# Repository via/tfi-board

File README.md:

# Testing hardware for TFI-computer

## Analog
Schematic and PCB for external TLC2543-based ADC board

 - Separate 5V supply to ADC and external sensors
 - Dedicated protected inputs for:
     * Battery Reference Voltage
     * Intake Temperature
     * Coolant Temperature
     * Throttle Position
     * Exhaust Gas Oxygen
     * Spare Thermistor
 - Addititional 5 unprotected inputs
 - SPI interface, and end-of-conversion output

## IO
Schematic and PCB for various digital IO and drivers

- 4x 0.5 Amp, 12 Volt ignition outputs
- 2x 2 Amp, 12 Volt high-side driver outputs
- 4x 2 Amp injector drivers
- 2x 2 amp low-side drivers
- CAN driver (Remove 3.3 V Zener to use 5V logic lines)
- 2 protected digital inputs

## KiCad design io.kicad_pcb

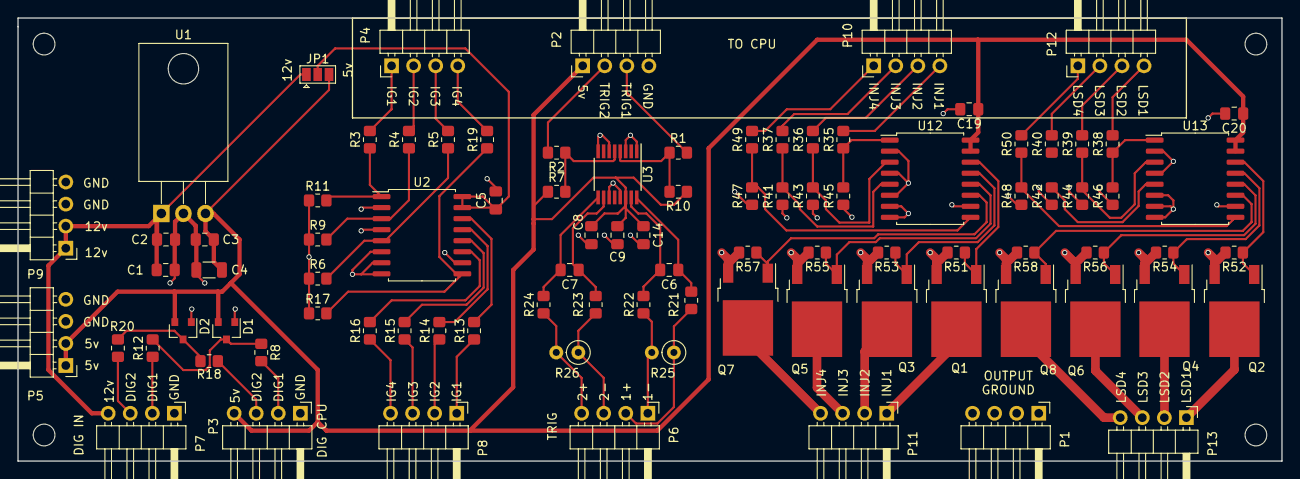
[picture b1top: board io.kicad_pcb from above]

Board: 2 copper layers, 145.5 x 51.0 mm, 91 parts (0 on the bottom side), 71 nets.

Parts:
C1: 10 uF; C_0805_2012Metric_Pad1.18x1.45mm_HandSolder
C2, C3: 0.1 uF; C_0805_2012Metric_Pad1.18x1.45mm_HandSolder
C4: 47 uF; C_1206_3216Metric
C5, C19, C20: 1 uF; C_0805_2012Metric_Pad1.18x1.45mm_HandSolder
C6, C7: 1n; C_0805_2012Metric_Pad1.18x1.45mm_HandSolder
C8: 10n; C_0805_2012Metric_Pad1.18x1.45mm_HandSolder
C9: 0.1u; C_0805_2012Metric_Pad1.18x1.45mm_HandSolder
C14: 1u; C_0805_2012Metric_Pad1.18x1.45mm_HandSolder
D1, D2: BAT54S; SOT-23
JP1: IG_PWR; SolderJumper-3_P1.3mm_Open_Pad1.0x1.5mm
P1: OUT_GND; PinHeader_1x04_P2.54mm_Horizontal
P2: TRIG-cpu; PinHeader_1x04_P2.54mm_Horizontal
P3: DIG-CPU; PinHeader_1x04_P2.54mm_Horizontal
P4: IN-CPU; PinHeader_1x04_P2.54mm_Horizontal
P5: CPU_PWR; PinHeader_1x04_P2.54mm_Horizontal
P6: TRIG-IN; PinHeader_1x04_P2.54mm_Horizontal
P7: DIG-IN; PinHeader_1x04_P2.54mm_Horizontal
P8: IGNITION; PinHeader_1x04_P2.54mm_Horizontal
P9: PWR_IN; PinHeader_1x04_P2.54mm_Horizontal
P10: INJ-CPU; PinHeader_1x04_P2.54mm_Horizontal
P11: INJECTORS; PinHeader_1x04_P2.54mm_Horizontal
P12: LSD-CPU; PinHeader_1x04_P2.54mm_Horizontal
P13: LSDS; PinHeader_1x04_P2.54mm_Horizontal
Q1, Q2, Q3, Q4, Q5, Q6, Q7, Q8: MOSFET; TO-252-2
R1, R2, R3, R4, R5, R8, R12, R18, R19, R20, R21, R22, R23, R24, R35, R36, R37, R38, R39, R40, R49, R50: 1k; R_0805_2012Metric_Pad1.20x1.40mm_HandSolder
R6, R9, R11, R17, R41, R42, R43, R44, R45, R46, R47, R48, R51, R52, R53, R54, R55, R56, R57, R58: 100k; R_0805_2012Metric_Pad1.20x1.40mm_HandSolder
R7, R10: 10k; R_0805_2012Metric_Pad1.20x1.40mm_HandSolder
R13, R14, R15, R16: 150; R_0805_2012Metric_Pad1.20x1.40mm_HandSolder
R25, R26: 330; R_Axial_DIN0207_L6.3mm_D2.5mm_P2.54mm_Vertical
U1: LM2940; TO-220-3_Horizontal_TabDown
U2, U12, U13: MIC4469; SOIC-16W_7.5x10.3mm_P1.27mm
U3: MAX9926UAEE+; QSOP-16_3.9x4.9mm_P0.635mm

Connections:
5v: C3.1, C4.1, C8.1, C9.1, C14.1, C19.1, C20.1, D1.2, D2.2, JP1.3, P2.1, P3.4, P5.1, P5.2, R7.1, R10.1, U1.3, U3.14, U12.15, U12.16, U13.15, U13.16
12v_power: C1.1, C2.1, JP1.1, P7.4, P9.1, P9.2, U1.1
DIG1-cpu: P3.2, R8.2
DIG1-in: P7.2, R12.1
DIG2-cpu: P3.3, R18.2
DIG2-in: P7.3, R20.1
GND: C1.2, C2.2, C3.2, C4.2, C5.2, C8.2, C9.2, C14.2, C19.2, C20.2, D1.1, D2.1, P2.4, P3.1, P5.3, P5.4, P7.1, P9.3, P9.4, R6.1, R9.1, R11.1, R17.1, R41.1, R42.1, R43.1, R44.1, R45.1, R46.1, R47.1, R48.1, U1.2, U2.2, U2.4, U2.6, U2.7, U2.8, U2.10, U3.1, U3.3, U3.6, U3.8, U3.11, U3.13, U12.2, U12.4, U12.6, U12.7, U12.8, U12.10, U13.2, U13.4, U13.6, U13.7, U13.8, U13.10
IG1-cpu: P4.1, R3.2
IG1-out: P8.1, R13.1
IG2-cpu: P4.2, R4.2
IG2-out: P8.2, R14.1
IG3-cpu: P4.3, R5.2
IG3-out: P8.3, R15.1
IG4-cpu: P4.4, R19.2
IG4-out: P8.4, R16.1
INJ1-cpu: P10.4, R35.2
INJ1-out: P11.1, Q1.2
INJ2-cpu: P10.3, R36.2
INJ2-out: P11.2, Q3.2
INJ3-cpu: P10.2, R37.2
INJ3-out: P11.3, Q5.2
INJ4-cpu: P10.1, R49.2
INJ4-out: P11.4, Q7.2
LSD1-cpu: P12.4, R38.2
LSD1-out: P13.1, Q2.2
LSD2-cpu: P12.3, R39.2
LSD2-out: P13.2, Q4.2
LSD3-cpu: P12.2, R40.2
LSD3-out: P13.3, Q6.2
LSD4-cpu: P12.1, R50.2
LSD4-out: P13.4, Q8.2
unnamed: C5.1, JP1.2, U2.15, U2.16
unnamed: C6.1, R21.2, U3.16
unnamed: C6.2, R22.2, U3.15
unnamed: C7.1, R23.2, U3.10
unnamed: C7.2, R24.2, U3.9
unnamed: D1.3, R8.1, R12.2
unnamed: D2.3, R18.1, R20.2
unnamed: Q1.1, R51.1, U12.14
unnamed: Q2.1, R52.1, U13.14
unnamed: Q3.1, R53.1, U12.13
unnamed: Q4.1, R54.1, U13.13
unnamed: Q5.1, R55.1, U12.12
unnamed: Q6.1, R56.1, U13.12
unnamed: Q7.1, R57.1, U12.11
unnamed: Q8.1, R58.1, U13.11
unnamed: R1.1, R10.2, U3.4
unnamed: R2.1, R7.2, U3.5
unnamed: R4.1, R9.2, U2.3
unnamed: R5.1, R6.2, U2.5
unnamed: R3.1, R11.2, U2.1
unnamed: R13.2, U2.14
unnamed: R14.2, U2.13
unnamed: R15.2, U2.12
unnamed: R16.2, U2.11
unnamed: R17.2, R19.1, U2.9
unnamed: R35.1, R45.2, U12.1
unnamed: R36.1, R43.2, U12.3
unnamed: R37.1, R41.2, U12.5
unnamed: R38.1, R46.2, U13.1
unnamed: R39.1, R44.2, U13.3
unnamed: R40.1, R42.2, U13.5
unnamed: R47.2, R49.1, U12.9
unnamed: R48.2, R50.1, U13.9
OUT_GND: P1.1, P1.2, P1.3, P1.4, Q1.3, Q2.3, Q3.3, Q4.3, Q5.3, Q6.3, Q7.3, Q8.3, R51.2, R52.2, R53.2, R54.2, R55.2, R56.2, R57.2, R58.2
TRIG1: P2.3, R1.2
TRIG1IN+: P6.2, R21.1, R25.1
TRIG1IN-: P6.1, R22.1, R25.2
TRIG2: P2.2, R2.2
TRIG2IN+: P6.4, R24.1, R26.2
TRIG2IN-: P6.3, R23.1, R26.1

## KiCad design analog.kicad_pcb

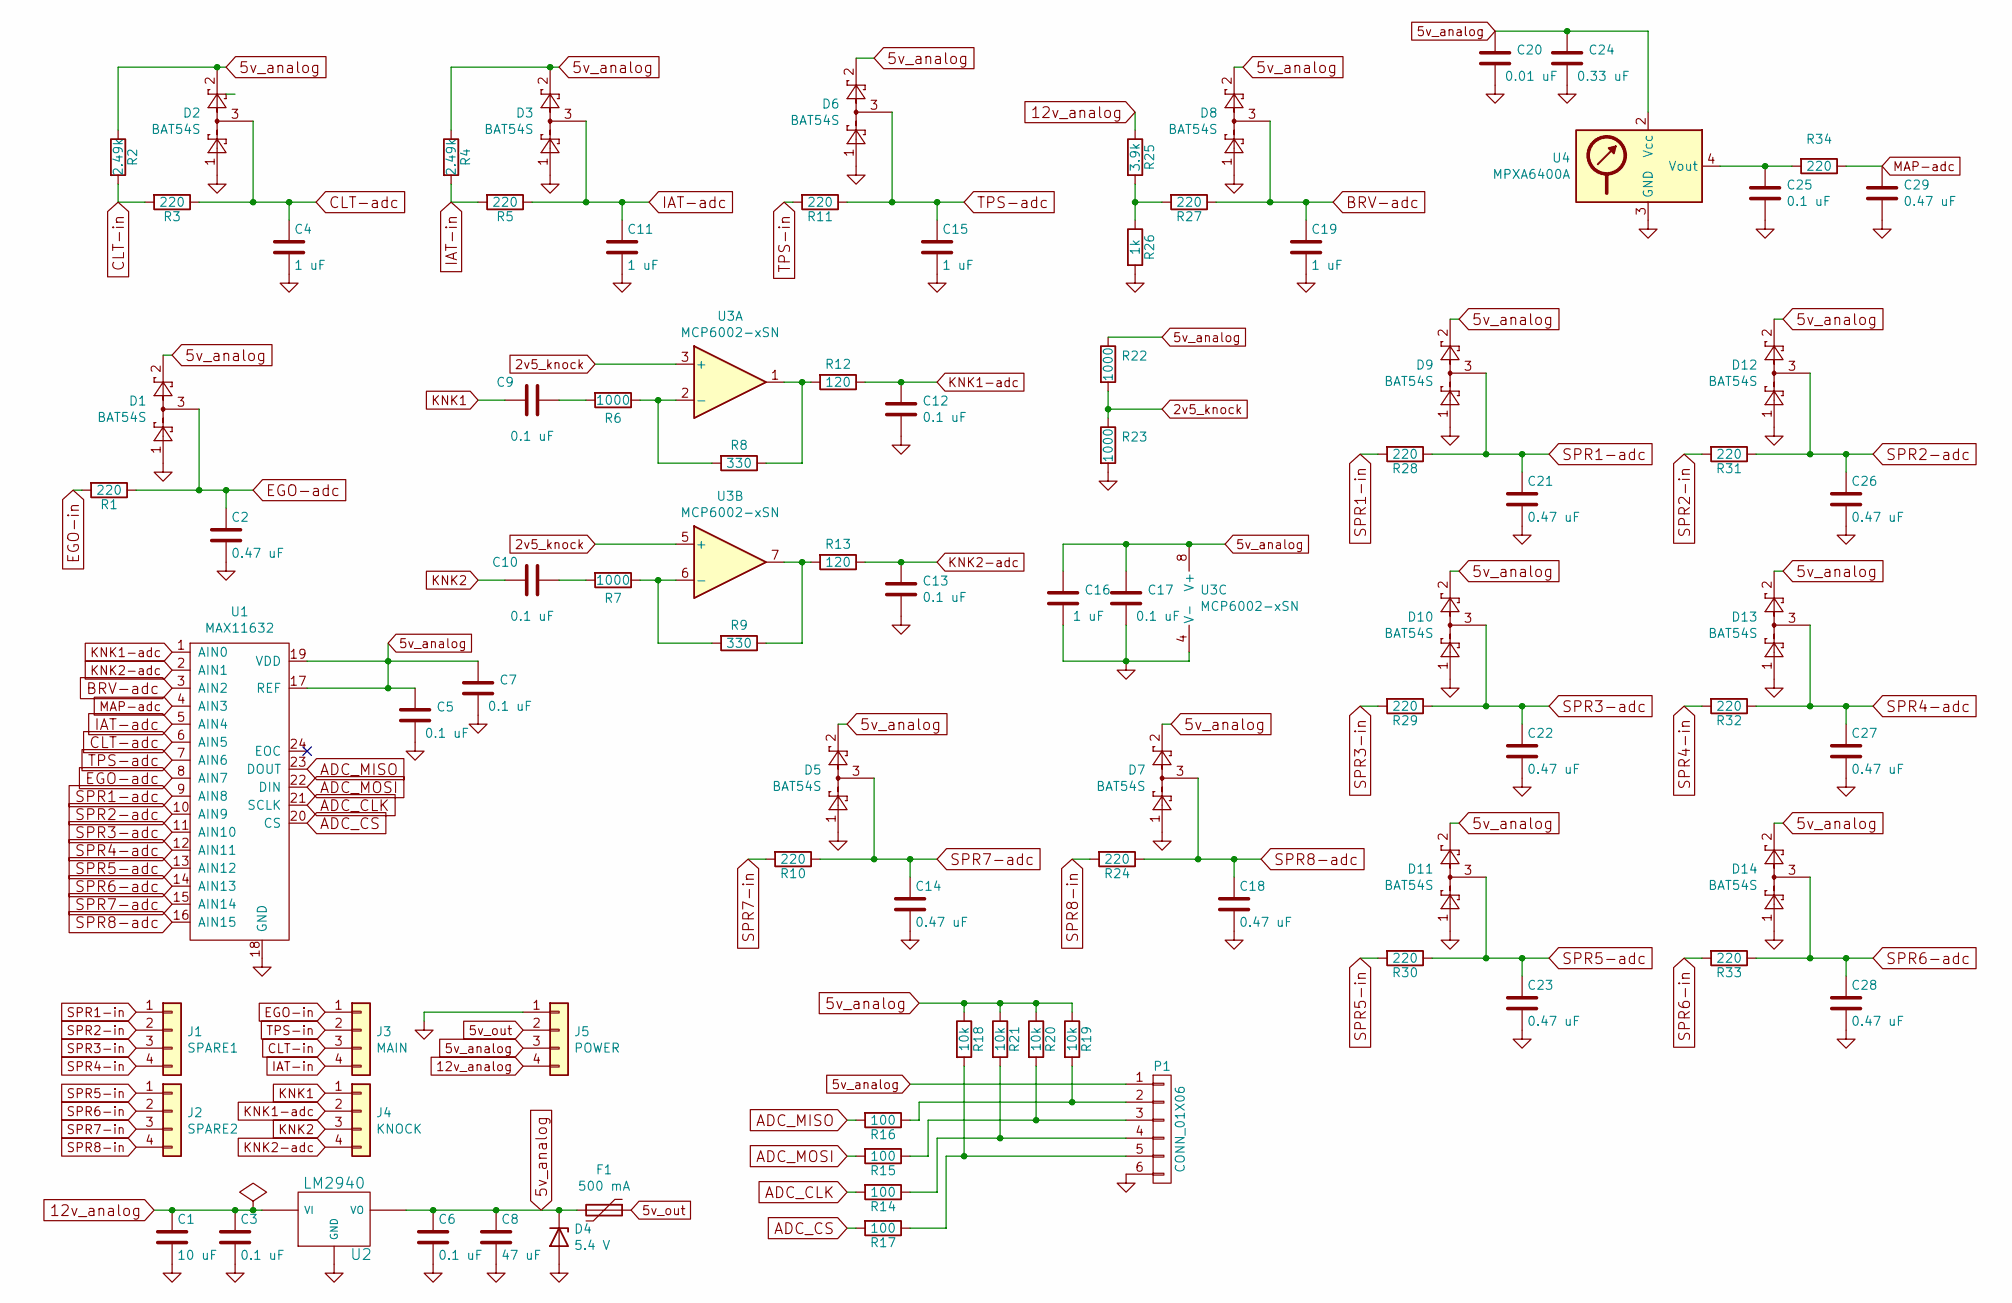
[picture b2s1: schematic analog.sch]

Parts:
C1: 10 uF; C_0805_2012Metric_Pad1.18x1.45mm_HandSolder; Rating 35V Tantalum
C2, C14, C18, C21, C22, C23, C26, C27, C28, C29: 0.47 uF; C_0805_2012Metric_Pad1.18x1.45mm_HandSolder
C3, C5, C6, C7, C9, C10, C12, C13, C17, C25: 0.1 uF; C_0805_2012Metric_Pad1.18x1.45mm_HandSolder
C4, C11, C15, C16, C19: 1 uF; C_0805_2012Metric_Pad1.18x1.45mm_HandSolder
C8: 47 uF; C_1206_3216Metric_Pad1.33x1.80mm_HandSolder; Rating 10 V Tantalum
C20: 0.01 uF; C_0805_2012Metric_Pad1.18x1.45mm_HandSolder
C24: 0.33 uF; C_0805_2012Metric_Pad1.18x1.45mm_HandSolder
D1, D2, D3, D5, D6, D7, D8, D9, D10, D11, D12, D13, D14: BAT54S; SOT-23
D4: 5.4 V; D_A-405_P2.54mm_Vertical_AnodeUp
F1: 500 mA; Fuse_1206_3216Metric_Pad1.42x1.75mm_HandSolder
J1: SPARE1; PinHeader_1x04_P2.54mm_Horizontal
J2: SPARE2; PinHeader_1x04_P2.54mm_Horizontal
J3: MAIN; PinHeader_1x04_P2.54mm_Horizontal
J4: KNOCK; PinHeader_1x04_P2.54mm_Horizontal
J5: POWER; PinHeader_1x04_P2.54mm_Horizontal
P1: CONN_01X06; PinHeader_1x06_P2.54mm_Horizontal
R1, R3, R5, R10, R11, R24, R27, R28, R29, R30, R31, R32, R33, R34: 220; R_0805_2012Metric_Pad1.20x1.40mm_HandSolder
R2, R4: 2.49k; R_0805_2012Metric_Pad1.20x1.40mm_HandSolder; Rating 0.1%
R6, R7, R22, R23: 1000; R_0805_2012Metric_Pad1.20x1.40mm_HandSolder
R8, R9: 330; R_0805_2012Metric_Pad1.20x1.40mm_HandSolder
R12, R13: 120; R_0805_2012Metric_Pad1.20x1.40mm_HandSolder
R14, R15, R16, R17: 100; R_0805_2012Metric_Pad1.20x1.40mm_HandSolder
R18, R19, R20, R21: 10k; R_0805_2012Metric_Pad1.20x1.40mm_HandSolder
R25: 3.9k; R_0805_2012Metric_Pad1.20x1.40mm_HandSolder; Rating 0.1%
R26: 1k; R_0805_2012Metric_Pad1.20x1.40mm_HandSolder; Rating 0.1%
U1: MAX11632; QSOP-24_3.9x8.7mm_P0.635mm
U2: LM2940; TO-220-3_Horizontal_TabDown
U3: MCP6002-xSN; MSOP-8_3x3mm_P0.65mm
U4: MPXA6400A; Freescale_98ARH99089A

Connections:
2v5_knock: R22.2, R23.1, U3.3 (+), U3.5 (+)
5v_analog: C5.1, C6.1, C7.1, C8.1, C16.1, C17.1, C20.1, C24.1, D1.2, D2.2, D3.2, D4.1 (K), D5.2, D6.2, D7.2, D8.2, D9.2, D10.2, D11.2, D12.2, D13.2, D14.2, F1.2, J5.3, P1.1, R2.1, R4.1, R18.1, R19.1, R20.1, R21.1, R22.1, U1.17 (REF), U1.19 (VDD), U2.3 (VO), U3.8 (V+), U4.2 (Vcc)
5v_out: F1.1, J5.2
12v_analog: C1.1, C3.1, J5.4, R25.1, U2.1 (VI)
ADC_CLK: R14.2, U1.21 (SCLK)
ADC_CS: R17.2, U1.20 (CS)
ADC_MISO: R16.2, U1.23 (DOUT)
ADC_MOSI: R15.2, U1.22 (DIN)
BRV-adc: C19.1, D8.3, R27.1, U1.3 (AIN2)
CLT-adc: C4.1, D2.3, R3.1, U1.6 (AIN5)
CLT-in: J3.3, R2.2, R3.2
EGO-adc: C2.1, D1.3, R1.1, U1.8 (AIN7)
EGO-in: J3.1, R1.2
GND: C1.2, C2.2, C3.2, C4.2, C5.2, C6.2, C7.2, C8.2, C11.2, C12.2, C13.2, C14.2, C15.2, C16.2, C17.2, C18.2, C19.2, C20.2, C21.2, C22.2, C23.2, C24.2, C25.2, C26.2, C27.2, C28.2, C29.2, D1.1, D2.1, D3.1, D4.2 (A), D5.1, D6.1, D7.1, D8.1, D9.1, D10.1, D11.1, D12.1, D13.1, D14.1, J5.1, P1.6, R23.2, R26.2, U1.18 (GND), U2.2 (GND), U3.4 (V-), U4.3 (GND)
IAT-adc: C11.1, D3.3, R5.1, U1.5 (AIN4)
IAT-in: J3.4, R4.2, R5.2
KNK1: C9.2, J4.1
KNK1-adc: C12.1, J4.2, R12.1, U1.1 (AIN0)
KNK2: C10.2, J4.3
KNK2-adc: C13.1, J4.4, R13.1, U1.2 (AIN1)
MAP-adc: C29.1, R34.1, U1.4 (AIN3)
unnamed: C9.1, R6.2
unnamed: C10.1, R7.2
unnamed: C25.1, R34.2, U4.4 (Vout)
unnamed: P1.2, R16.1, R19.2
unnamed: P1.3, R15.1, R20.2
unnamed: P1.4, R14.1, R21.2
unnamed: P1.5, R17.1, R18.2
unnamed: R6.1, R8.2, U3.2 (-)
unnamed: R7.1, R9.2, U3.6 (-)
unnamed: R8.1, R12.2, U3.1
unnamed: R9.1, R13.2, U3.7
unnamed: R25.2, R26.1, R27.2
SPR1-adc: C21.1, D9.3, R28.1, U1.9 (AIN8)
SPR1-in: J1.1, R28.2
SPR2-adc: C26.1, D12.3, R31.1, U1.10 (AIN9)
SPR2-in: J1.2, R31.2
SPR3-adc: C22.1, D10.3, R29.1, U1.11 (AIN10)
SPR3-in: J1.3, R29.2
SPR4-adc: C27.1, D13.3, R32.1, U1.12 (AIN11)
SPR4-in: J1.4, R32.2
SPR5-adc: C23.1, D11.3, R30.1, U1.13 (AIN12)
SPR5-in: J2.1, R30.2
SPR6-adc: C28.1, D14.3, R33.1, U1.14 (AIN13)
SPR6-in: J2.2, R33.2
SPR7-adc: C14.1, D5.3, R10.1, U1.15 (AIN14)
SPR7-in: J2.3, R10.2
SPR8-adc: C18.1, D7.3, R24.1, U1.16 (AIN15)
SPR8-in: J2.4, R24.2
TPS-adc: C15.1, D6.3, R11.1, U1.7 (AIN6)
TPS-in: J3.2, R11.2

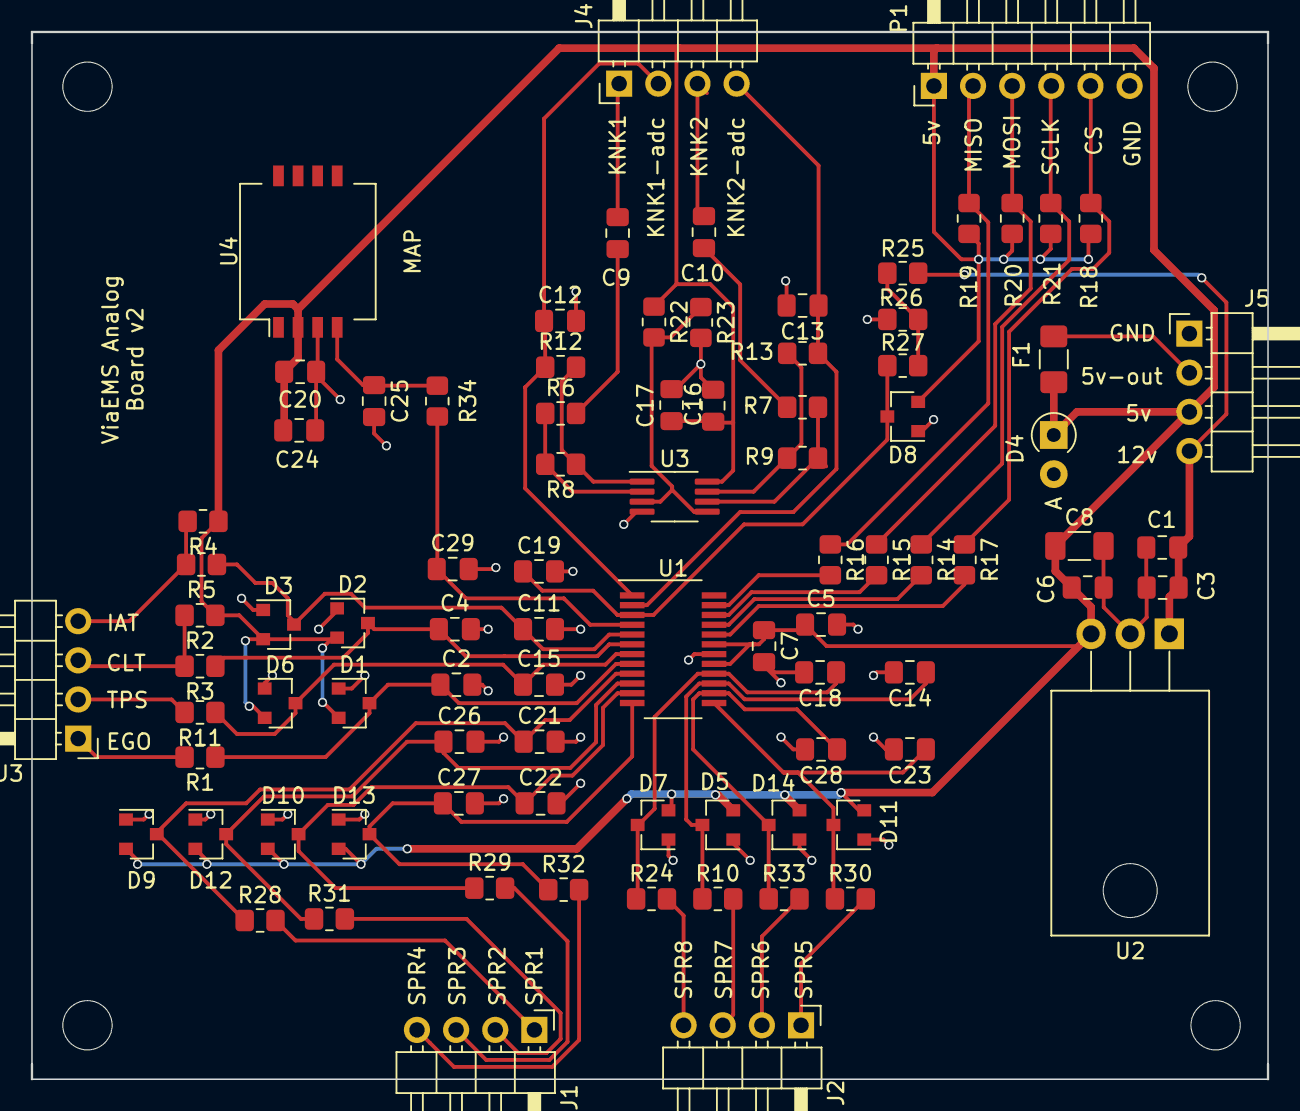
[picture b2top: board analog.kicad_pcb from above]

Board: 2 copper layers, 80.2 x 67.9 mm, 88 parts (0 on the bottom side), 51 nets.

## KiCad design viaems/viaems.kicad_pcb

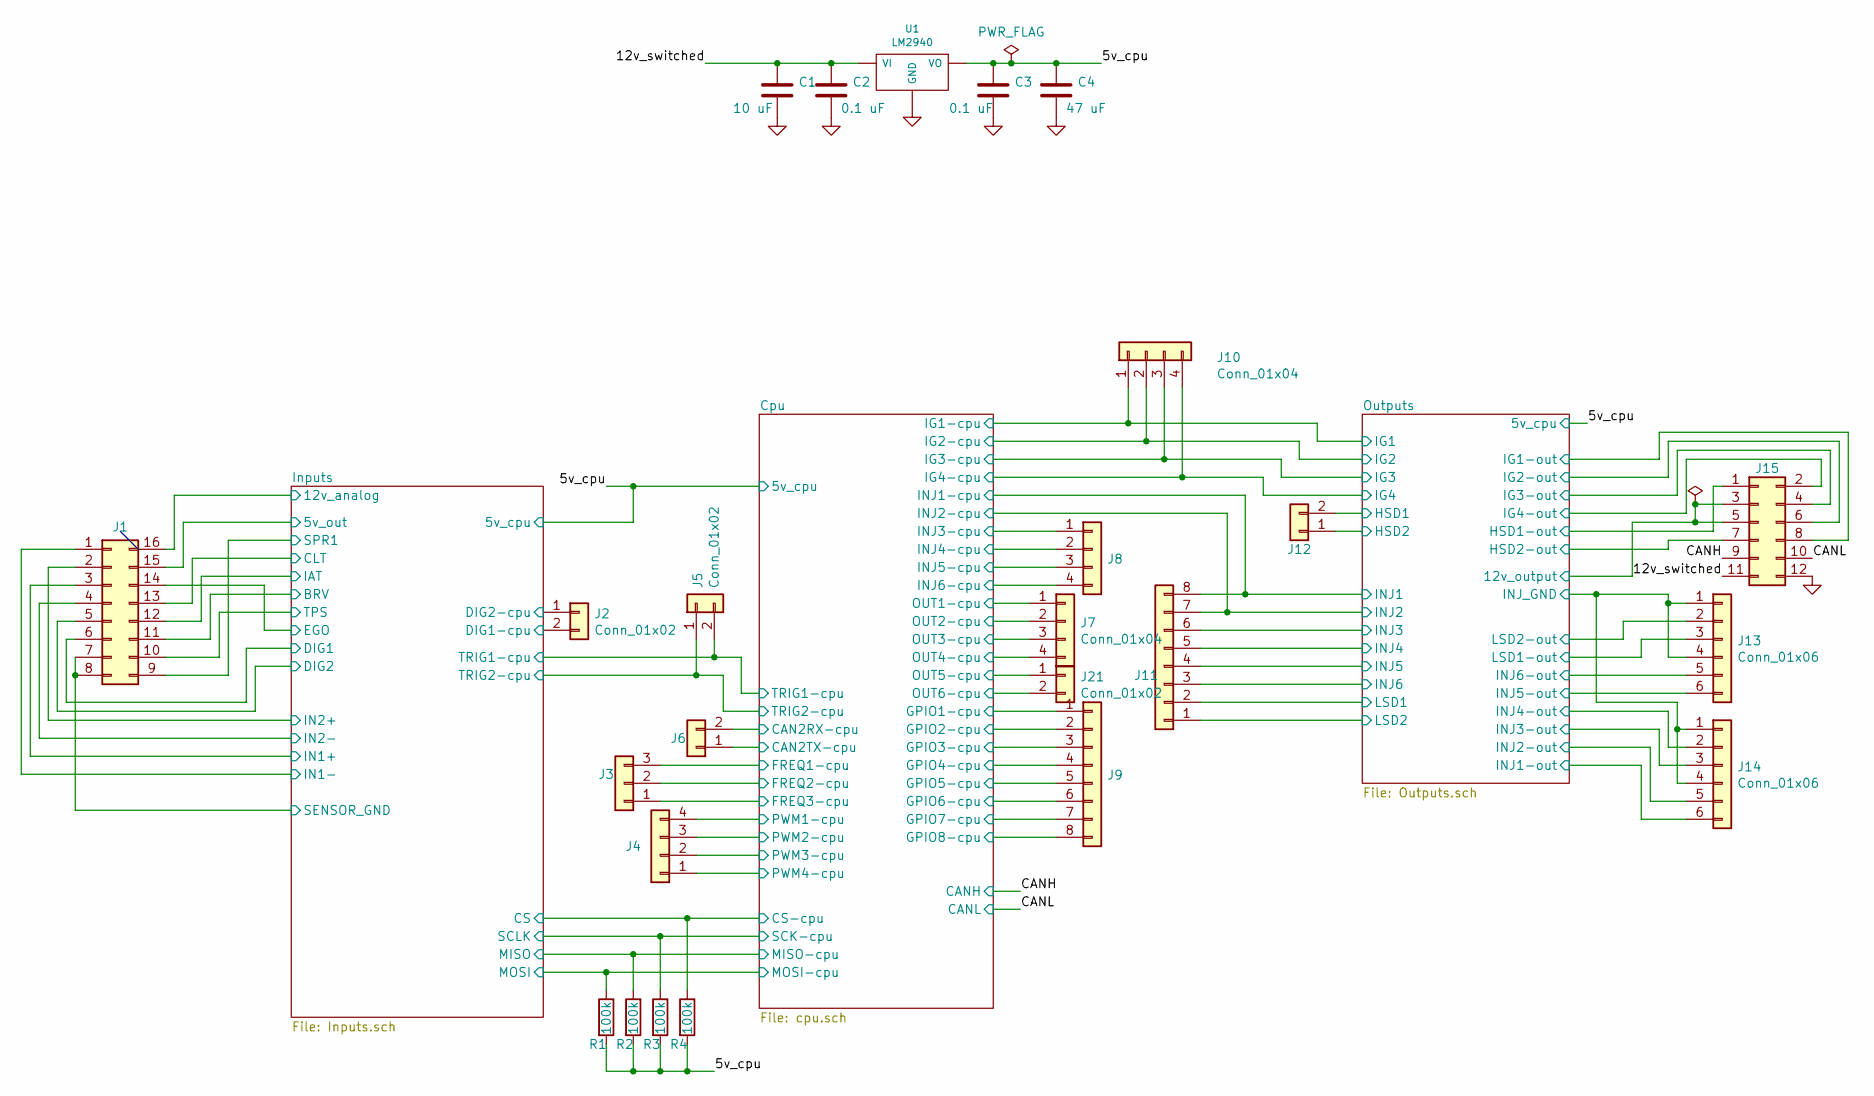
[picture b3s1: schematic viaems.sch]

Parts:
C1: 10 uF; C_1206_3216Metric_Pad1.42x1.75mm_HandSolder; Digikey-Part 445-8034-1-ND
C2, C3: 0.1 uF; C_0805_2012Metric_Pad1.15x1.40mm_HandSolder; Digikey-Part 478-10836-1-ND
C4: 47 uF; C_1206_3216Metric_Pad1.42x1.75mm_HandSolder; Digikey-Part 478-9009-1-ND
J1: Conn_02x08_Counter_Clockwise; PinHeader_2x08_P2.54mm_Vertical; Digikey-Part 609-3220-ND
J2, J5, J6, J12, J21: Conn_01x02; PinHeader_1x02_P2.54mm_Vertical; Digikey-Part 952-2262-ND
J3: Conn_01x03; PinHeader_1x03_P2.54mm_Vertical; Digikey-Part 732-5316-ND
J4, J7, J8, J10: Conn_01x04; PinHeader_1x04_P2.54mm_Vertical; Digikey-Part 732-5317-ND
J9, J11: Conn_01x08; PinHeader_1x08_P2.54mm_Vertical; Digikey-Part 732-5321-ND
J13, J14: Conn_01x06; PinHeader_1x06_P2.54mm_Vertical; Digikey-Part 732-5319-ND
J15: Conn_02x06_Odd_Even; PinHeader_2x06_P2.54mm_Vertical; Digikey-Part 732-5297-ND
R1, R2, R3, R4: 100k; R_0805_2012Metric_Pad1.15x1.40mm_HandSolder; Digikey-Part P100KDACT-ND
U1: LM2940; TO-220-3_Horizontal_TabDown; Digikey-Part LM2940T-5.0/NOPB-ND

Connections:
5v_cpu: C3.1, C4.1, R1.2, R2.2, R3.2, R4.2, U1.3 (VO); also elsewhere on the board
/12v_switched: C1.1, C2.1, J15.11, U1.1 (VI)
/CANH: J15.9; also elsewhere on the board
/CANL: J15.10; also elsewhere on the board
/Cpu/CAN2RX-cpu: J6.2; also elsewhere on the board
/Cpu/CAN2TX-cpu: J6.1; also elsewhere on the board
/Cpu/FREQ1-cpu: J3.3; also elsewhere on the board
/Cpu/FREQ2-cpu: J3.2; also elsewhere on the board
/Cpu/FREQ3-cpu: J3.1; also elsewhere on the board
/Cpu/GPIO1-cpu: J9.1; also elsewhere on the board
/Cpu/GPIO2-cpu: J9.2; also elsewhere on the board
/Cpu/GPIO3-cpu: J9.3; also elsewhere on the board
/Cpu/GPIO4-cpu: J9.4; also elsewhere on the board
/Cpu/GPIO5-cpu: J9.5; also elsewhere on the board
/Cpu/GPIO6-cpu: J9.6; also elsewhere on the board
/Cpu/GPIO7-cpu: J9.7; also elsewhere on the board
/Cpu/GPIO8-cpu: J9.8; also elsewhere on the board
/Cpu/INJ3-cpu: J8.1; also elsewhere on the board
/Cpu/INJ4-cpu: J8.2; also elsewhere on the board
/Cpu/INJ5-cpu: J8.3; also elsewhere on the board
/Cpu/INJ6-cpu: J8.4; also elsewhere on the board
/Cpu/OUT1-cpu: J7.1; also elsewhere on the board
/Cpu/OUT2-cpu: J7.2; also elsewhere on the board
/Cpu/OUT3-cpu: J7.3; also elsewhere on the board
/Cpu/OUT4-cpu: J7.4; also elsewhere on the board
/Cpu/OUT5-cpu: J21.1; also elsewhere on the board
/Cpu/OUT6-cpu: J21.2; also elsewhere on the board
/Cpu/PWM1-cpu: J4.4; also elsewhere on the board
/Cpu/PWM2-cpu: J4.3; also elsewhere on the board
/Cpu/PWM3-cpu: J4.2; also elsewhere on the board
/Cpu/PWM4-cpu: J4.1; also elsewhere on the board
/Cpu/SCK-cpu: R3.1; also elsewhere on the board
/Cpu/TRIG1-cpu: J5.2; also elsewhere on the board
/Cpu/TRIG2-cpu: J5.1; also elsewhere on the board
/Inputs/5v_out: J1.15; also elsewhere on the board
/Inputs/12v_analog: J1.16; also elsewhere on the board
/Inputs/BRV: J1.11; also elsewhere on the board
/Inputs/CLT: J1.13; also elsewhere on the board
/Inputs/CS: R4.1; also elsewhere on the board
/Inputs/DIG1: J1.6; also elsewhere on the board
/Inputs/DIG1-cpu: J2.2; also elsewhere on the board
/Inputs/DIG2: J1.5; also elsewhere on the board
/Inputs/DIG2-cpu: J2.1; also elsewhere on the board
/Inputs/EGO: J1.14; also elsewhere on the board
/Inputs/IAT: J1.12; also elsewhere on the board
/Inputs/IN1+: J1.3; also elsewhere on the board
/Inputs/IN1-: J1.1; also elsewhere on the board
/Inputs/IN2+: J1.2; also elsewhere on the board
/Inputs/IN2-: J1.4; also elsewhere on the board
/Inputs/MISO: R2.1; also elsewhere on the board
/Inputs/MOSI: R1.1; also elsewhere on the board
/Inputs/SPR1: J1.9; also elsewhere on the board
/Inputs/TPS: J1.10; also elsewhere on the board
/Outputs/12v_output: J15.3, J15.5; also elsewhere on the board
/Outputs/HSD1: J12.2; also elsewhere on the board
/Outputs/HSD1-out: J15.1; also elsewhere on the board
/Outputs/HSD2: J12.1; also elsewhere on the board
/Outputs/HSD2-out: J15.7; also elsewhere on the board
/Outputs/IG1: J10.1; also elsewhere on the board
/Outputs/IG1-out: J15.8; also elsewhere on the board
/Outputs/IG2: J10.2; also elsewhere on the board
/Outputs/IG2-out: J15.6; also elsewhere on the board
/Outputs/IG3: J10.3; also elsewhere on the board
/Outputs/IG3-out: J15.4; also elsewhere on the board
/Outputs/IG4: J10.4; also elsewhere on the board
/Outputs/IG4-out: J15.2; also elsewhere on the board
/Outputs/INJ1: J11.8; also elsewhere on the board
/Outputs/INJ1-out: J14.6; also elsewhere on the board
/Outputs/INJ2: J11.7; also elsewhere on the board
/Outputs/INJ2-out: J14.5; also elsewhere on the board
/Outputs/INJ3: J11.6; also elsewhere on the board
/Outputs/INJ3-out: J14.3; also elsewhere on the board
/Outputs/INJ4: J11.5; also elsewhere on the board
/Outputs/INJ4-out: J14.2; also elsewhere on the board
/Outputs/INJ5: J11.4; also elsewhere on the board
/Outputs/INJ5-out: J13.6; also elsewhere on the board
/Outputs/INJ6: J11.3; also elsewhere on the board
/Outputs/INJ6-out: J13.5; also elsewhere on the board
/Outputs/INJ_GND: J13.1, J13.4, J14.1, J14.4; also elsewhere on the board
/Outputs/LSD1: J11.2; also elsewhere on the board
/Outputs/LSD1-out: J13.3; also elsewhere on the board
/Outputs/LSD2: J11.1; also elsewhere on the board
/Outputs/LSD2-out: J13.2; also elsewhere on the board
GND: C1.2, C2.2, C3.2, C4.2, J1.7, J1.8, J15.12, U1.2 (GND); also elsewhere on the board

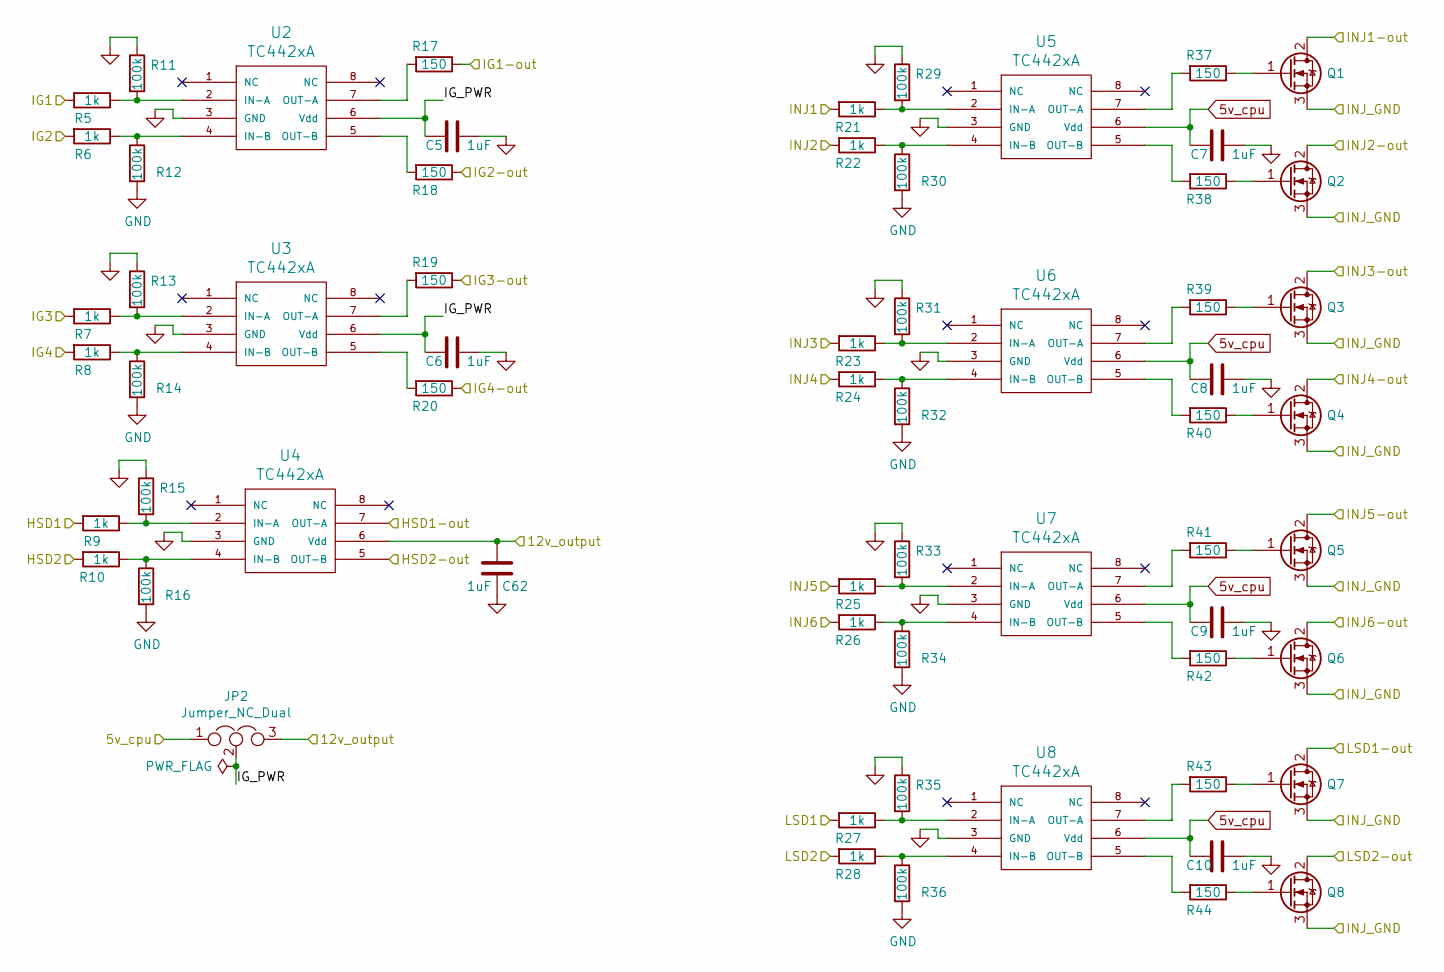
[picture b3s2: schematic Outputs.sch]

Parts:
C5, C6, C7, C8, C9, C10, C62: 1uF; C_0805_2012Metric_Pad1.15x1.40mm_HandSolder; Digikey-Part 1276-1029-1-ND
JP2: Jumper_NC_Dual; PinHeader_1x03_P2.54mm_Vertical; Digikey-Part 732-5316-ND
Q1, Q2, Q3, Q4, Q5, Q6, Q7, Q8: VND7NV04; TO-252-2; Digikey-Part 497-11707-1-ND
R5, R6, R7, R8, R9, R10, R21, R22, R23, R24, R25, R26, R27, R28: 1k; R_0805_2012Metric_Pad1.15x1.40mm_HandSolder; Digikey-Part RNCP0805FTD1K00CT-ND
R11, R12, R13, R14, R15, R16, R29, R30, R31, R32, R33, R34, R35, R36: 100k; R_0805_2012Metric_Pad1.15x1.40mm_HandSolder; Digikey-Part P100KDACT-ND
R17, R18, R19, R20: 150; R_2512_6332Metric_Pad1.52x3.35mm_HandSolder; Digikey-Part 541-150XCT-ND
R37, R38, R39, R40, R41, R42, R43, R44: 150; R_0805_2012Metric_Pad1.15x1.40mm_HandSolder; Digikey-Part RNCP0805FTD150RCT-ND
U2, U3, U4, U5, U6, U7, U8: TC442xA; SOIC-8_3.9x4.9mm_P1.27mm; Digikey-Part TC4427EOA713CT-ND

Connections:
5v_cpu: C7.2, C8.2, C9.2, C10.2, JP2.1, U5.6 (Vdd), U6.6 (Vdd), U7.6 (Vdd), U8.6 (Vdd); also elsewhere on the board
/Outputs/12v_output: C62.2, JP2.3, U4.6 (Vdd); also elsewhere on the board
/Outputs/HSD1: R9.2; also elsewhere on the board
/Outputs/HSD1-out: U4.7 (OUT-A); also elsewhere on the board
/Outputs/HSD2: R10.2; also elsewhere on the board
/Outputs/HSD2-out: U4.5 (OUT-B); also elsewhere on the board
/Outputs/IG1: R5.2; also elsewhere on the board
/Outputs/IG1-out: R17.1; also elsewhere on the board
/Outputs/IG2: R6.2; also elsewhere on the board
/Outputs/IG2-out: R18.1; also elsewhere on the board
/Outputs/IG3: R7.2; also elsewhere on the board
/Outputs/IG3-out: R19.1; also elsewhere on the board
/Outputs/IG4: R8.2; also elsewhere on the board
/Outputs/IG4-out: R20.1; also elsewhere on the board
/Outputs/IG_PWR: C5.2, C6.2, JP2.2, U2.6 (Vdd), U3.6 (Vdd)
/Outputs/INJ1: R21.2; also elsewhere on the board
/Outputs/INJ1-out: Q1.2 (D); also elsewhere on the board
/Outputs/INJ2: R22.2; also elsewhere on the board
/Outputs/INJ2-out: Q2.2 (D); also elsewhere on the board
/Outputs/INJ3: R23.2; also elsewhere on the board
/Outputs/INJ3-out: Q3.2 (D); also elsewhere on the board
/Outputs/INJ4: R24.2; also elsewhere on the board
/Outputs/INJ4-out: Q4.2 (D); also elsewhere on the board
/Outputs/INJ5: R25.2; also elsewhere on the board
/Outputs/INJ5-out: Q5.2 (D); also elsewhere on the board
/Outputs/INJ6: R26.2; also elsewhere on the board
/Outputs/INJ6-out: Q6.2 (D); also elsewhere on the board
/Outputs/INJ_GND: Q1.3 (S), Q2.3 (S), Q3.3 (S), Q4.3 (S), Q5.3 (S), Q6.3 (S), Q7.3 (S), Q8.3 (S); also elsewhere on the board
/Outputs/LSD1: R27.2; also elsewhere on the board
/Outputs/LSD1-out: Q7.2 (D); also elsewhere on the board
/Outputs/LSD2: R28.2; also elsewhere on the board
/Outputs/LSD2-out: Q8.2 (D); also elsewhere on the board
GND: C5.1, C6.1, C7.1, C8.1, C9.1, C10.1, C62.1, R11.1, R12.2, R13.1, R14.2, R15.1, R16.2, R29.1, R30.2, R31.1, R32.2, R33.1, R34.2, R35.1, R36.2, U2.3 (GND), U3.3 (GND), U4.3 (GND), U5.3 (GND), U6.3 (GND), U7.3 (GND), U8.3 (GND); also elsewhere on the board
unnamed: Q1.1 (G), R37.1
unnamed: Q2.1 (G), R38.1
unnamed: Q3.1 (G), R39.1
unnamed: Q4.1 (G), R40.1
unnamed: Q5.1 (G), R41.1
unnamed: Q6.1 (G), R42.1
unnamed: Q7.1 (G), R43.1
unnamed: Q8.1 (G), R44.1
unnamed: R10.1, R16.1, U4.4 (IN-B)
unnamed: R5.1, R11.2, U2.2 (IN-A)
unnamed: R6.1, R12.1, U2.4 (IN-B)
unnamed: R7.1, R13.2, U3.2 (IN-A)
unnamed: R8.1, R14.1, U3.4 (IN-B)
unnamed: R9.1, R15.2, U4.2 (IN-A)
unnamed: R17.2, U2.7 (OUT-A)
unnamed: R18.2, U2.5 (OUT-B)
unnamed: R19.2, U3.7 (OUT-A)
unnamed: R20.2, U3.5 (OUT-B)
unnamed: R21.1, R29.2, U5.2 (IN-A)
unnamed: R22.1, R30.1, U5.4 (IN-B)
unnamed: R23.1, R31.2, U6.2 (IN-A)
unnamed: R24.1, R32.1, U6.4 (IN-B)
unnamed: R25.1, R33.2, U7.2 (IN-A)
unnamed: R26.1, R34.1, U7.4 (IN-B)
unnamed: R27.1, R35.2, U8.2 (IN-A)
unnamed: R28.1, R36.1, U8.4 (IN-B)
unnamed: R37.2, U5.7 (OUT-A)
unnamed: R38.2, U5.5 (OUT-B)
unnamed: R39.2, U6.7 (OUT-A)
unnamed: R40.2, U6.5 (OUT-B)
unnamed: R41.2, U7.7 (OUT-A)
unnamed: R42.2, U7.5 (OUT-B)
unnamed: R43.2, U8.7 (OUT-A)
unnamed: R44.2, U8.5 (OUT-B)
